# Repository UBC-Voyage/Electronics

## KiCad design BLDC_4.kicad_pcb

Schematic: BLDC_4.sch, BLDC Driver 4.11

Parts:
C2, C3: 100n; SMD-0603_c
J1: RJ45; RJ45_Amphenol_54602-x08_Horizontal
K1: SERVO; pinhead-1X03
P4: IN+; 1PAD_4x5mm
P5: IN-; 1PAD_4x5mm
P6: MOTOR1; 1PAD_4x5mm
P7: MOTOR2; 1PAD_4x5mm
P9: MOTOR3; 1PAD_4x5mm
R3: 39k; SMD-0603_r
R4, R5: 2k2; SMD-0603_r
R6: 0R; SMD-0603_r
R53, R54: SHUNT; WSLP2726
R103, R104: 22R; SMD-0603_r
X1: MINI-USB-SHIELD-32005-201; USB-UX60R-MB-5ST

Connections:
+5V: J1.8, K1.2, R6.2; also elsewhere on the board
/CAN bus transceiver/CANH: J1.1; also elsewhere on the board
/CAN bus transceiver/CANL: J1.2; also elsewhere on the board
/MCU/AN_IN: C2.2, R3.2, R4.2; also elsewhere on the board
/MCU/SERVO: C3.2, R5.1; also elsewhere on the board
/MCU/USB_DM: R103.1; also elsewhere on the board
/MCU/USB_DP: R104.1; also elsewhere on the board
/Mosfet driver/H1_LOW: R53.2; also elsewhere on the board
/Mosfet driver/H1_VS: P9.1; also elsewhere on the board
/Mosfet driver/H2_VS: P7.1; also elsewhere on the board
/Mosfet driver/H3_LOW: R54.1; also elsewhere on the board
/Mosfet driver/H3_VS: P6.1; also elsewhere on the board
/Mosfet driver/SH1_A: R54.3; also elsewhere on the board
/Mosfet driver/SH1_B: R54.4; also elsewhere on the board
/Mosfet driver/SH2_A: R53.4; also elsewhere on the board
/Mosfet driver/SH2_B: R53.3; also elsewhere on the board
GND: C2.1, C3.1, J1.3, J1.6, J1.7, K1.3, P5.1, R4.1, R53.1, R54.2, X1.5; also elsewhere on the board
unnamed: K1.1, R5.2
unnamed: R6.1, X1.1
unnamed: R103.2, X1.2
unnamed: R104.2, X1.3
V_SUPPLY: P4.1, R3.1; also elsewhere on the board

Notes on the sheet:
100R if used as servo output
Mount 0R if used as USB host
ESD protection?
BLDC motor controller
Voltage supply (0 - 60v) Needs external decoupling caps to avoid high voltage transients produced by the inductance of the battery wiring while switching the FETs Also critical for EMI/RF compliance
Connect signal ground and power ground in one place only

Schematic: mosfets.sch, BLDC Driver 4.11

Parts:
Q1, Q2, Q3, Q4, Q5, Q6: IRFS7530; D2PAK-7-GDS
R28, R29, R34, R35, R42, R43: 4R7; SMD-0603_r
R30, R36, R46: 39k; SMD-0603_r

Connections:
/Mosfet driver/H1_LOW: Q2.S, R30.1, R36.1; also elsewhere on the board
/Mosfet driver/H1_VS: Q1.S, Q2.D; also elsewhere on the board
/Mosfet driver/H2_VS: Q3.S, Q4.D; also elsewhere on the board
/Mosfet driver/H3_LOW: Q6.S, R46.1; also elsewhere on the board
/Mosfet driver/H3_VS: Q5.S, Q6.D; also elsewhere on the board
/Mosfet driver/M_H1: R28.2; also elsewhere on the board
/Mosfet driver/M_H2: R34.2; also elsewhere on the board
/Mosfet driver/M_H3: R42.2; also elsewhere on the board
/Mosfet driver/M_L1: R29.2; also elsewhere on the board
/Mosfet driver/M_L2: R35.2; also elsewhere on the board
/Mosfet driver/M_L3: R43.2; also elsewhere on the board
GND: Q4.S; also elsewhere on the board
unnamed: Q1.G, R28.1
unnamed: Q2.G, R29.1, R30.2
unnamed: Q3.G, R34.1
unnamed: Q4.G, R35.1, R36.2
unnamed: Q5.G, R42.1
unnamed: Q6.G, R43.1, R46.2
V_SUPPLY: Q1.D, Q3.D, Q5.D; also elsewhere on the board

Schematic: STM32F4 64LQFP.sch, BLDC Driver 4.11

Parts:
C10, C11, C12, C13, C14, C16, C17, C31, C35: 2.2u; SMD-0603_c
C15, C38: 15p; SMD-0603_c
C32: 100n; SMD-0603_c
P2: SWD; MICRO_JST_6
U1: STM32F40X_LQFP64; lqfp64_pad_mod
X2: 8MHz 10ppm; Crystal_5x3mm; mfg# ABM3B-8.0-10-1UT

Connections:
/CAN bus transceiver/CAN_RX: U1.61; also elsewhere on the board
/CAN bus transceiver/CAN_TX: U1.62; also elsewhere on the board
/MCU/ADC_TEMP: U1.17; also elsewhere on the board
/MCU/AN_IN: U1.10; also elsewhere on the board
/MCU/BR_SO1: U1.27; also elsewhere on the board
/MCU/BR_SO2: U1.26; also elsewhere on the board
/MCU/DC_CAL: U1.33; also elsewhere on the board
/MCU/EN_GATE: U1.51; also elsewhere on the board
/MCU/FAULT: U1.53; also elsewhere on the board
/MCU/H1: U1.43; also elsewhere on the board
/MCU/H2: U1.42; also elsewhere on the board
/MCU/H3: U1.41; also elsewhere on the board
/MCU/HALL_1: U1.58
/MCU/HALL_2: U1.59
/MCU/HALL_3: U1.52
/MCU/L1: U1.36; also elsewhere on the board
/MCU/L2: U1.35; also elsewhere on the board
/MCU/L3: U1.34; also elsewhere on the board
/MCU/LED_GREEN: U1.24
/MCU/LED_RED: U1.25
/MCU/MISO_ADC_EXT2: U1.22
/MCU/RX_SCL_MOSI: U1.23, U1.29, U1.38
/MCU/SCK_ADC_EXT: U1.21
/MCU/SENS1: U1.16; also elsewhere on the board
/MCU/SENS2: U1.15; also elsewhere on the board
/MCU/SENS3: U1.14; also elsewhere on the board
/MCU/SERVO: U1.57; also elsewhere on the board
/MCU/TEMP_MOTOR: U1.8
/MCU/TX_SDA_NSS: U1.20, U1.30, U1.37
/MCU/USB_DM: U1.44; also elsewhere on the board
/MCU/USB_DP: U1.45; also elsewhere on the board
GND: C10.1, C11.1, C12.1, C13.1, C14.1, C15.2, C16.2, C17.2, C31.1, C32.1, C35.1, C38.2, P2.3, U1.12, U1.18, U1.60, U1.63, X2.3; also elsewhere on the board
NRST: C32.2, P2.5, U1.7
unnamed: C15.1, U1.5, X2.1
unnamed: C16.1, U1.31
unnamed: C17.1, U1.47
unnamed: C38.1, U1.6, X2.2
SWCLK: P2.2, U1.49
SWDIO: P2.4, U1.46
VCC: C10.2, C11.2, C12.2, C13.2, C14.2, C31.2, C35.2, P2.1, U1.1, U1.13, U1.19, U1.32, U1.48, U1.64; also elsewhere on the board

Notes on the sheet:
Programming / Debug connector
Reset pin internally pulled up
Required for USB to work
Bypass, place next to VDD pins

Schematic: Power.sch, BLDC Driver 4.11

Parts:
C1, C8, C9, C39, C40, C43, C44, C49: 10u,50V; SMD-1206
C18, C20, C23, C24, C26, C52: 2.2u; SMD-0603_c
C19: 120p; SMD-0603_c
C21: 6.8n; SMD-0603_c
C22: 22n; SMD-0603_c
C25, C33: 100u; c_tant_B
C27: 100n; SMD-0603_c
C28, C29, C30: 220n; SMD-0603_c
C34, C36: 2.2n; SMD-0603_c
C37: 15u,100V; c_2220
C51: 15u, 100v; c_2220
D4: DIODESCH; SMA_Handsoldering
D5: TVS 5V; do214ac
L1: 22u; inductor_smd_8x5mm
R17: 18k; SMD-0603_r
R18: 3k3; SMD-0603_r
R19: 15k; SMD-0603_r
R20: 10k; SMD-0603_r
R21: 220k; SMD-0603_r
R23, R26, R32: 39k; SMD-0603_r
R24, R27, R33: 2k2; SMD-0603_r
R25: 1M; SMD-0603_r
R48, R49, R50, R51: 100R; SMD-0603_r
U2: TC2117; SOT-223
U3: DRV8302; TSSOP-56-PP

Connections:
+5V: C33.1, D5.2, L1.2, R17.1, U2.3; also elsewhere on the board
/MCU/BR_SO1: U3.25; also elsewhere on the board
/MCU/BR_SO2: U3.26; also elsewhere on the board
/MCU/DC_CAL: U3.12; also elsewhere on the board
/MCU/EN_GATE: U3.16; also elsewhere on the board
/MCU/FAULT: U3.6; also elsewhere on the board
/MCU/H1: U3.17; also elsewhere on the board
/MCU/H2: U3.19; also elsewhere on the board
/MCU/H3: U3.21; also elsewhere on the board
/MCU/L1: U3.18; also elsewhere on the board
/MCU/L2: U3.20; also elsewhere on the board
/MCU/L3: U3.22; also elsewhere on the board
/MCU/SENS1: R23.2, R24.2; also elsewhere on the board
/MCU/SENS2: R26.2, R27.2; also elsewhere on the board
/MCU/SENS3: R32.2, R33.2; also elsewhere on the board
/Mosfet driver/H1_LOW: U3.44; also elsewhere on the board
/Mosfet driver/H1_VS: C28.1, R32.1, U3.46; also elsewhere on the board
/Mosfet driver/H2_VS: C29.1, R26.1, U3.41; also elsewhere on the board
/Mosfet driver/H3_LOW: U3.34; also elsewhere on the board
/Mosfet driver/H3_VS: C30.1, R23.1, U3.36; also elsewhere on the board
/Mosfet driver/M_H1: U3.47; also elsewhere on the board
/Mosfet driver/M_H2: U3.42; also elsewhere on the board
/Mosfet driver/M_H3: U3.37; also elsewhere on the board
/Mosfet driver/M_L1: U3.45; also elsewhere on the board
/Mosfet driver/M_L2: U3.40; also elsewhere on the board
/Mosfet driver/M_L3: U3.35; also elsewhere on the board
/Mosfet driver/SH1_A: R48.1; also elsewhere on the board
/Mosfet driver/SH1_B: R49.1; also elsewhere on the board
/Mosfet driver/SH2_A: R50.1; also elsewhere on the board
/Mosfet driver/SH2_B: R51.1; also elsewhere on the board
GND: C1.1, C8.1, C9.1, C18.2, C19.1, C20.1, C21.1, C23.1, C24.2, C25.2, C26.2, C33.2, C37.1, C39.1, C40.1, C43.2, C44.2, C49.2, C51.1, C52.1, D5.1, R18.2, R20.2, R21.1, R24.1, R25.1, R27.1, R33.1, U2.1, U3.8, U3.10, U3.28, U3.39, U3.57; also elsewhere on the board
unnamed: C18.1, C26.1, U3.13
unnamed: C19.2, R19.2, U3.2
unnamed: C20.2, C52.2, U3.11, U3.23
unnamed: C21.2, R19.1
unnamed: C22.1, U3.14
unnamed: C22.2, U3.15
unnamed: C23.2, U3.27
unnamed: C27.1, L1.1, U3.50, U3.51
unnamed: C27.2, U3.52
unnamed: C28.2, U3.48
unnamed: C29.2, U3.43
unnamed: C30.2, U3.38
unnamed: C34.1, R48.2, U3.33
unnamed: C34.2, R49.2, U3.32
unnamed: C36.1, R50.2, U3.31
unnamed: C36.2, R51.2, U3.30
unnamed: R17.2, R18.1, U3.3
unnamed: R20.1, U3.7
unnamed: R21.2, U3.1
unnamed: R25.2, U3.49
VCC: C24.1, C25.1, U2.2, U3.9, U3.24; also elsewhere on the board
V_SUPPLY: C1.2, C8.2, C9.2, C37.2, C39.2, C40.2, C43.1, C44.1, C49.1, C51.2, U3.29, U3.53, U3.54; also elsewhere on the board

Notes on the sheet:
MCU must sense the voltage at each phase
3.3v regulator for the logic

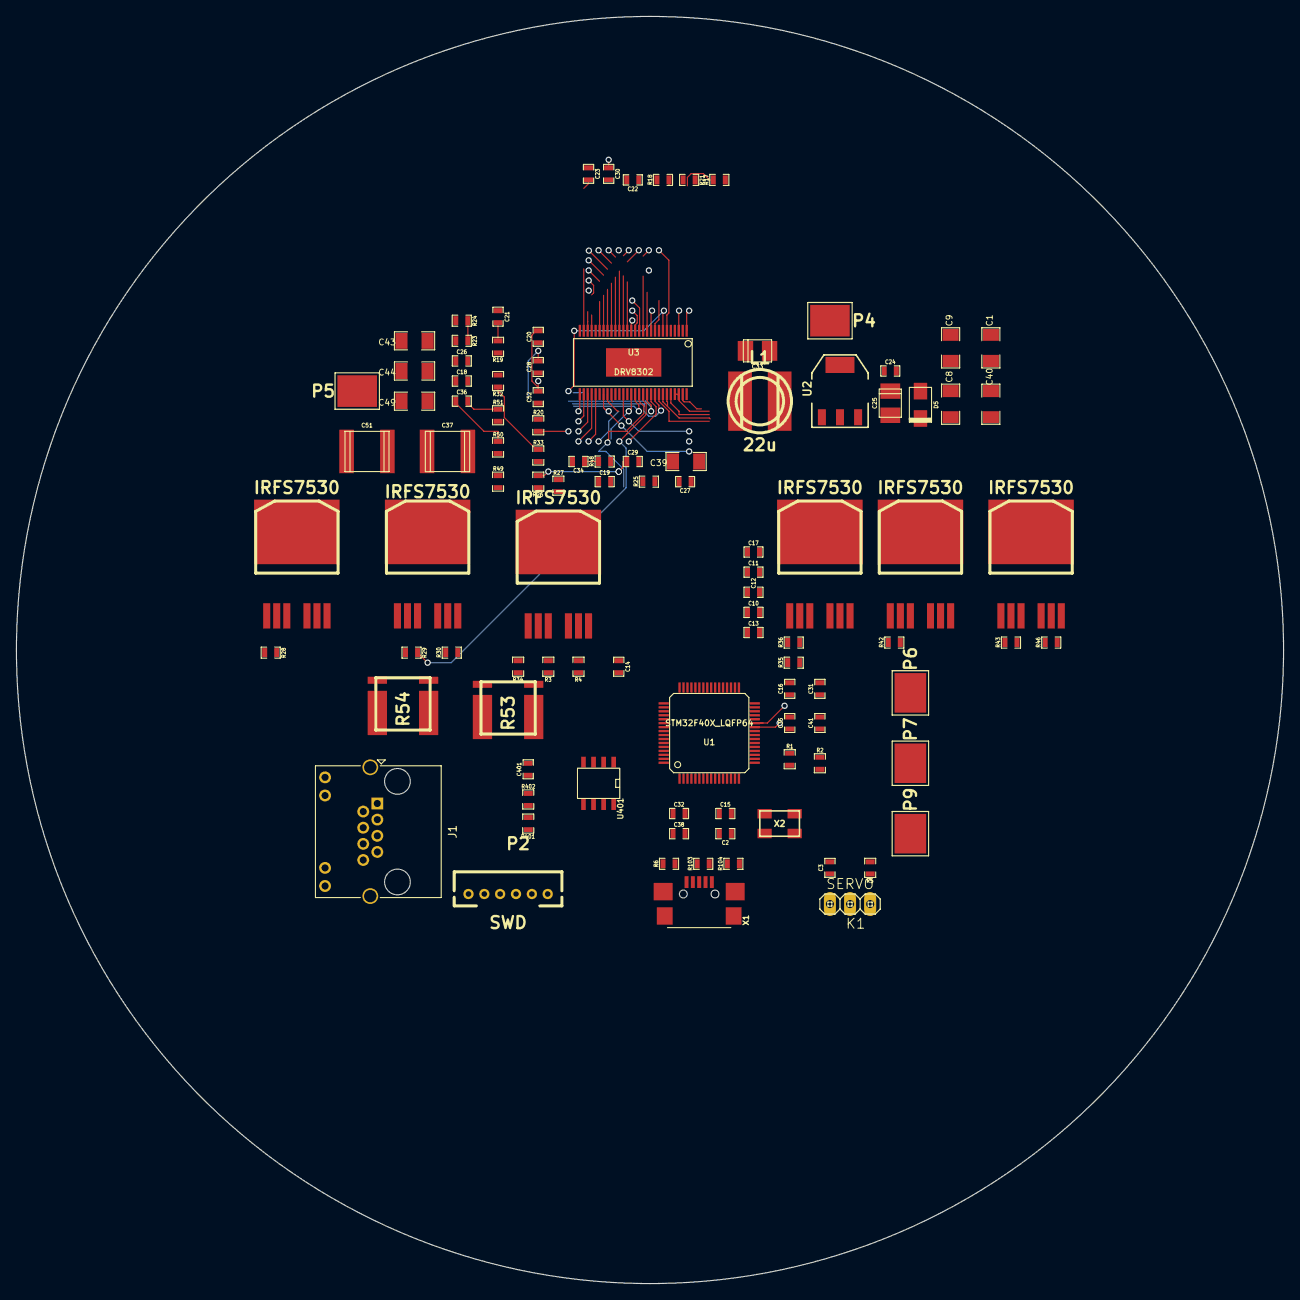
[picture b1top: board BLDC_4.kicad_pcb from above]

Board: 2 copper layers, 160.0 x 160.0 mm, 102 parts (0 on the bottom side), 82 nets.

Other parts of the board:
C41, C401: 2.2u; SMD-0603_c
R1: NTC 10k; SMD-0603_r
R2, R402: 10k; SMD-0603_r
R401: NI; SMD-0603_r
U401: SN65HVD232; SOIC-8-W

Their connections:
/CAN bus transceiver/CANH: R401.1, U401.7; also elsewhere on the board
/CAN bus transceiver/CANL: R401.2, U401.6; also elsewhere on the board
/CAN bus transceiver/CAN_RX: U401.4; also elsewhere on the board
/CAN bus transceiver/CAN_TX: U401.1; also elsewhere on the board
/MCU/ADC_TEMP: C41.1, R1.2, R2.1; also elsewhere on the board
GND: C41.2, C401.2, R2.2, R402.2, U401.2; also elsewhere on the board
unnamed: R402.1, U401.8
VCC: C401.1, R1.1, U401.3; also elsewhere on the board

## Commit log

2018-10-14 Bill of Materials
2018-10-17 no message
2018-10-28 First Commit of Altium Project
2018-11-09 Motor Controlor, Somewhat done
2018-11-22 Schematic Complete- Missing Footprints for mosfet driver and shunt resistors are still missing. Error associating schematic diagrams with footprints.
2018-11-22 Restructured directories
2018-11-24 fixing footprint issue
2018-11-28 finished footprint for DRV8302
